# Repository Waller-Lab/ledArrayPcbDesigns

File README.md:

# ledArrayPcbDesigns
LED Array PCB Designs for various Arrays

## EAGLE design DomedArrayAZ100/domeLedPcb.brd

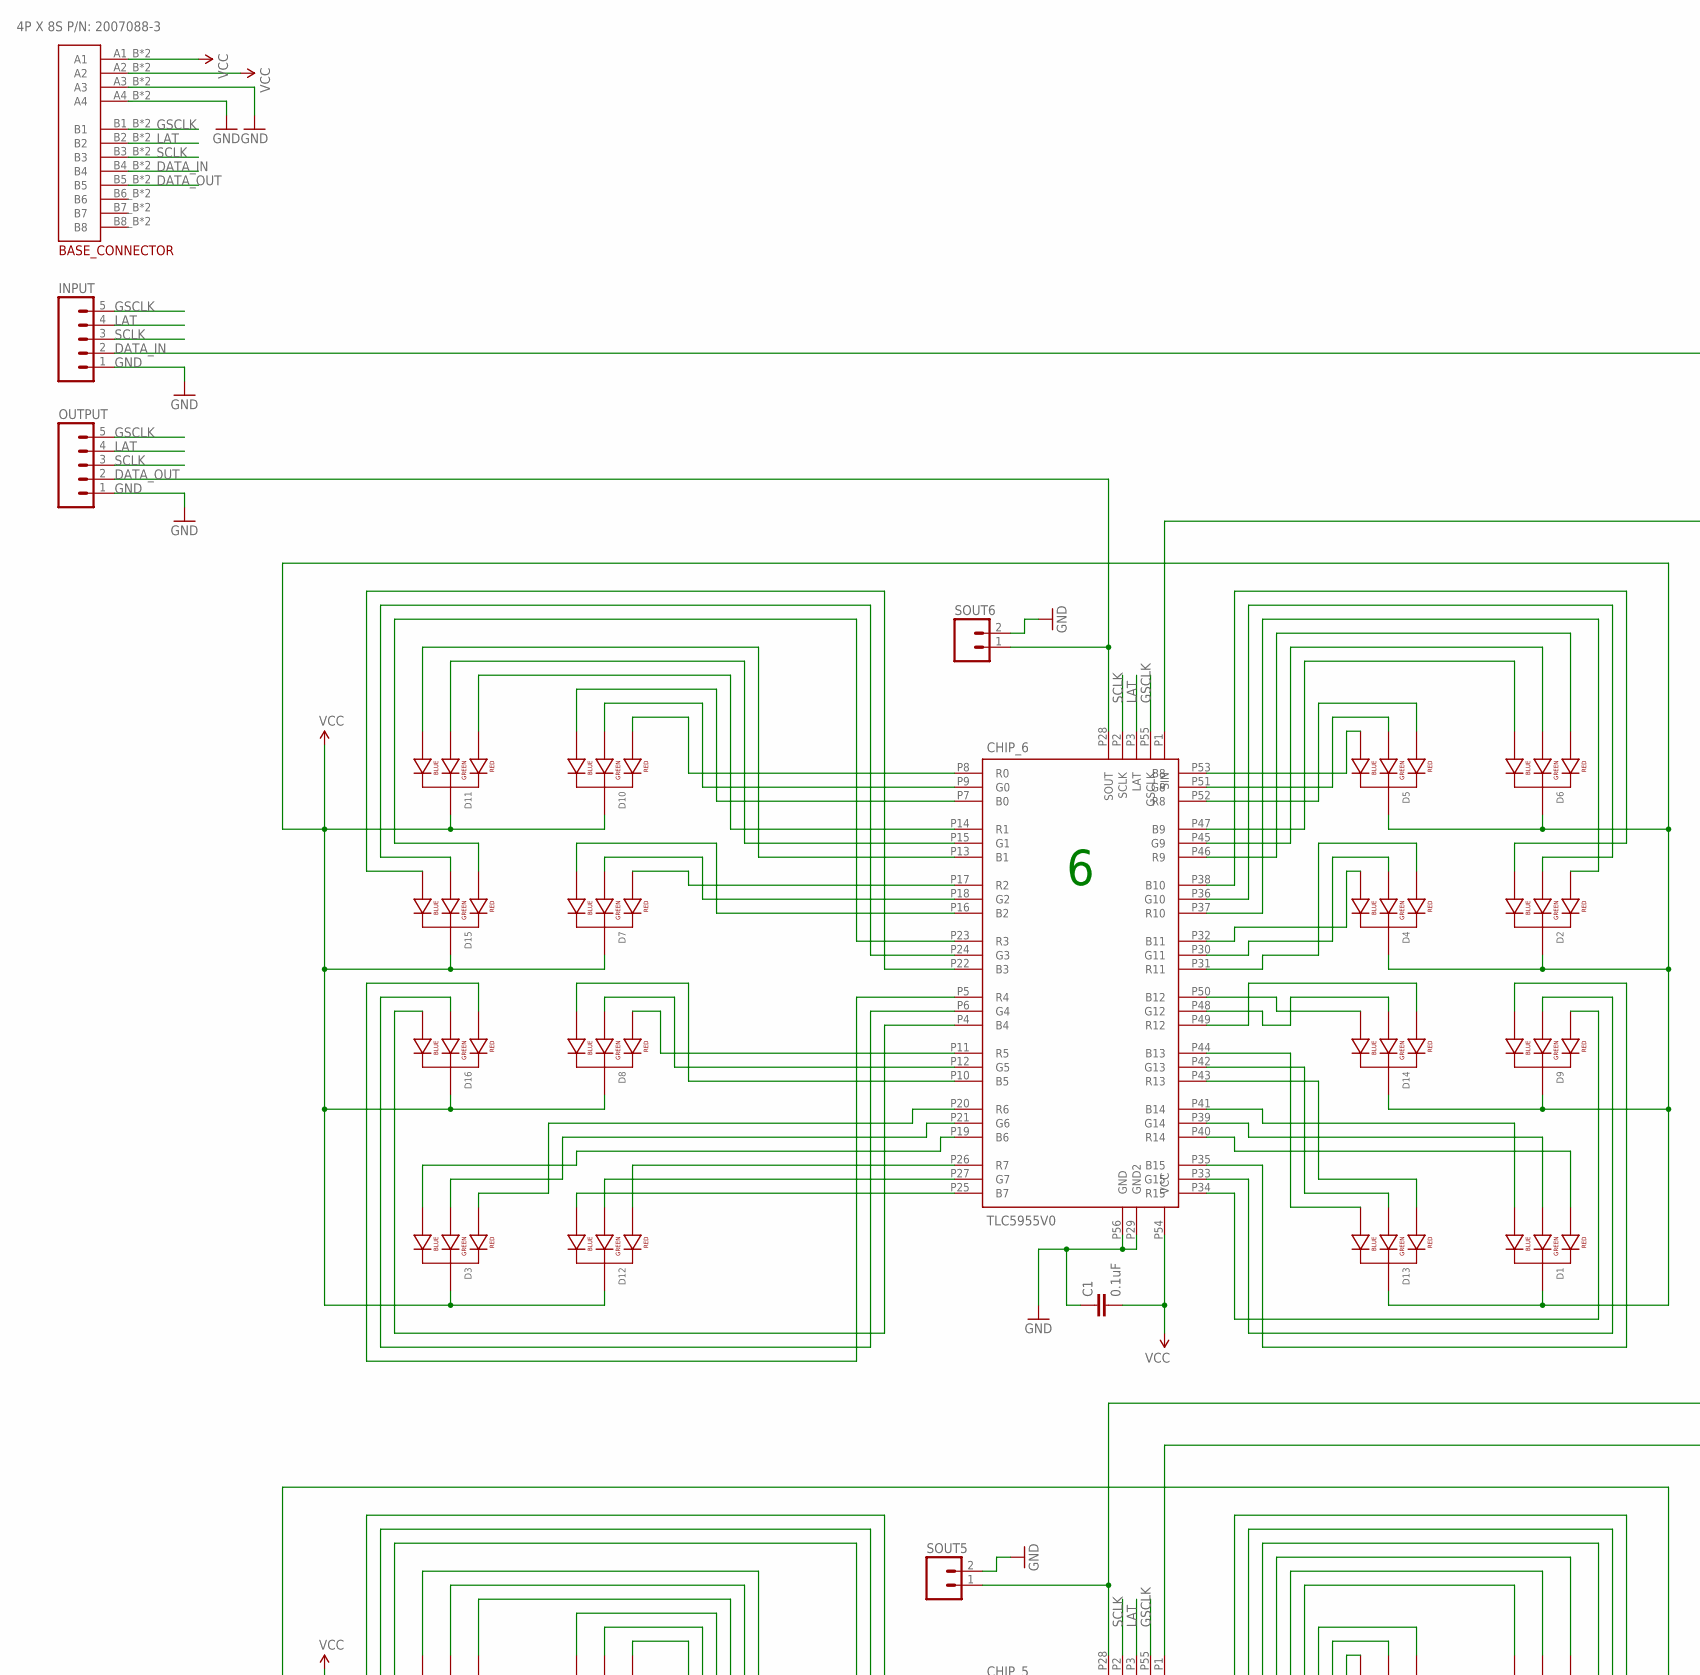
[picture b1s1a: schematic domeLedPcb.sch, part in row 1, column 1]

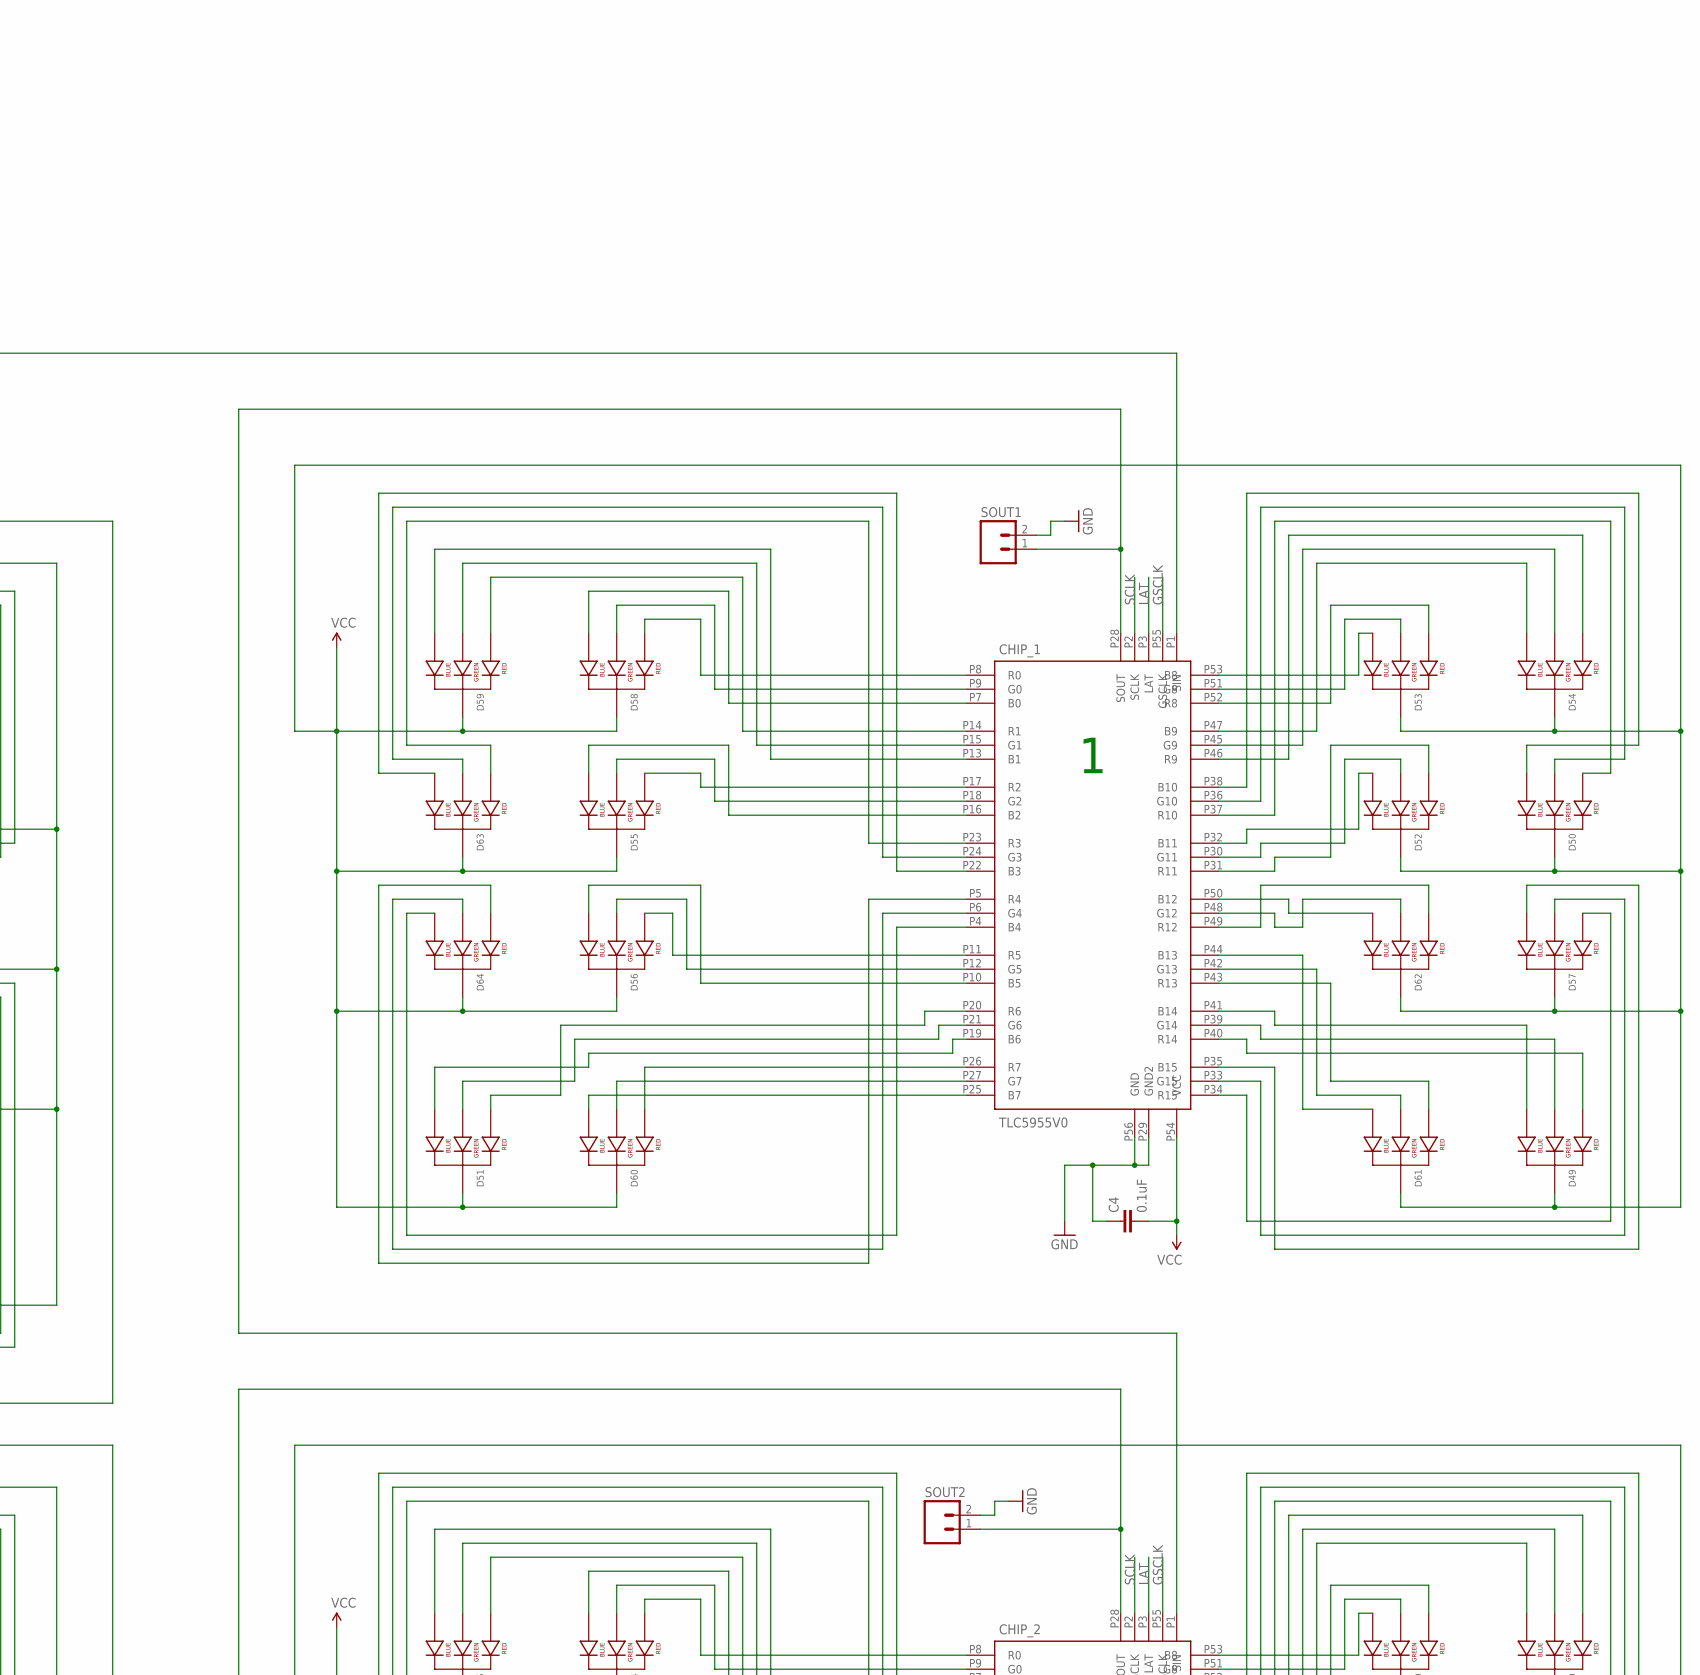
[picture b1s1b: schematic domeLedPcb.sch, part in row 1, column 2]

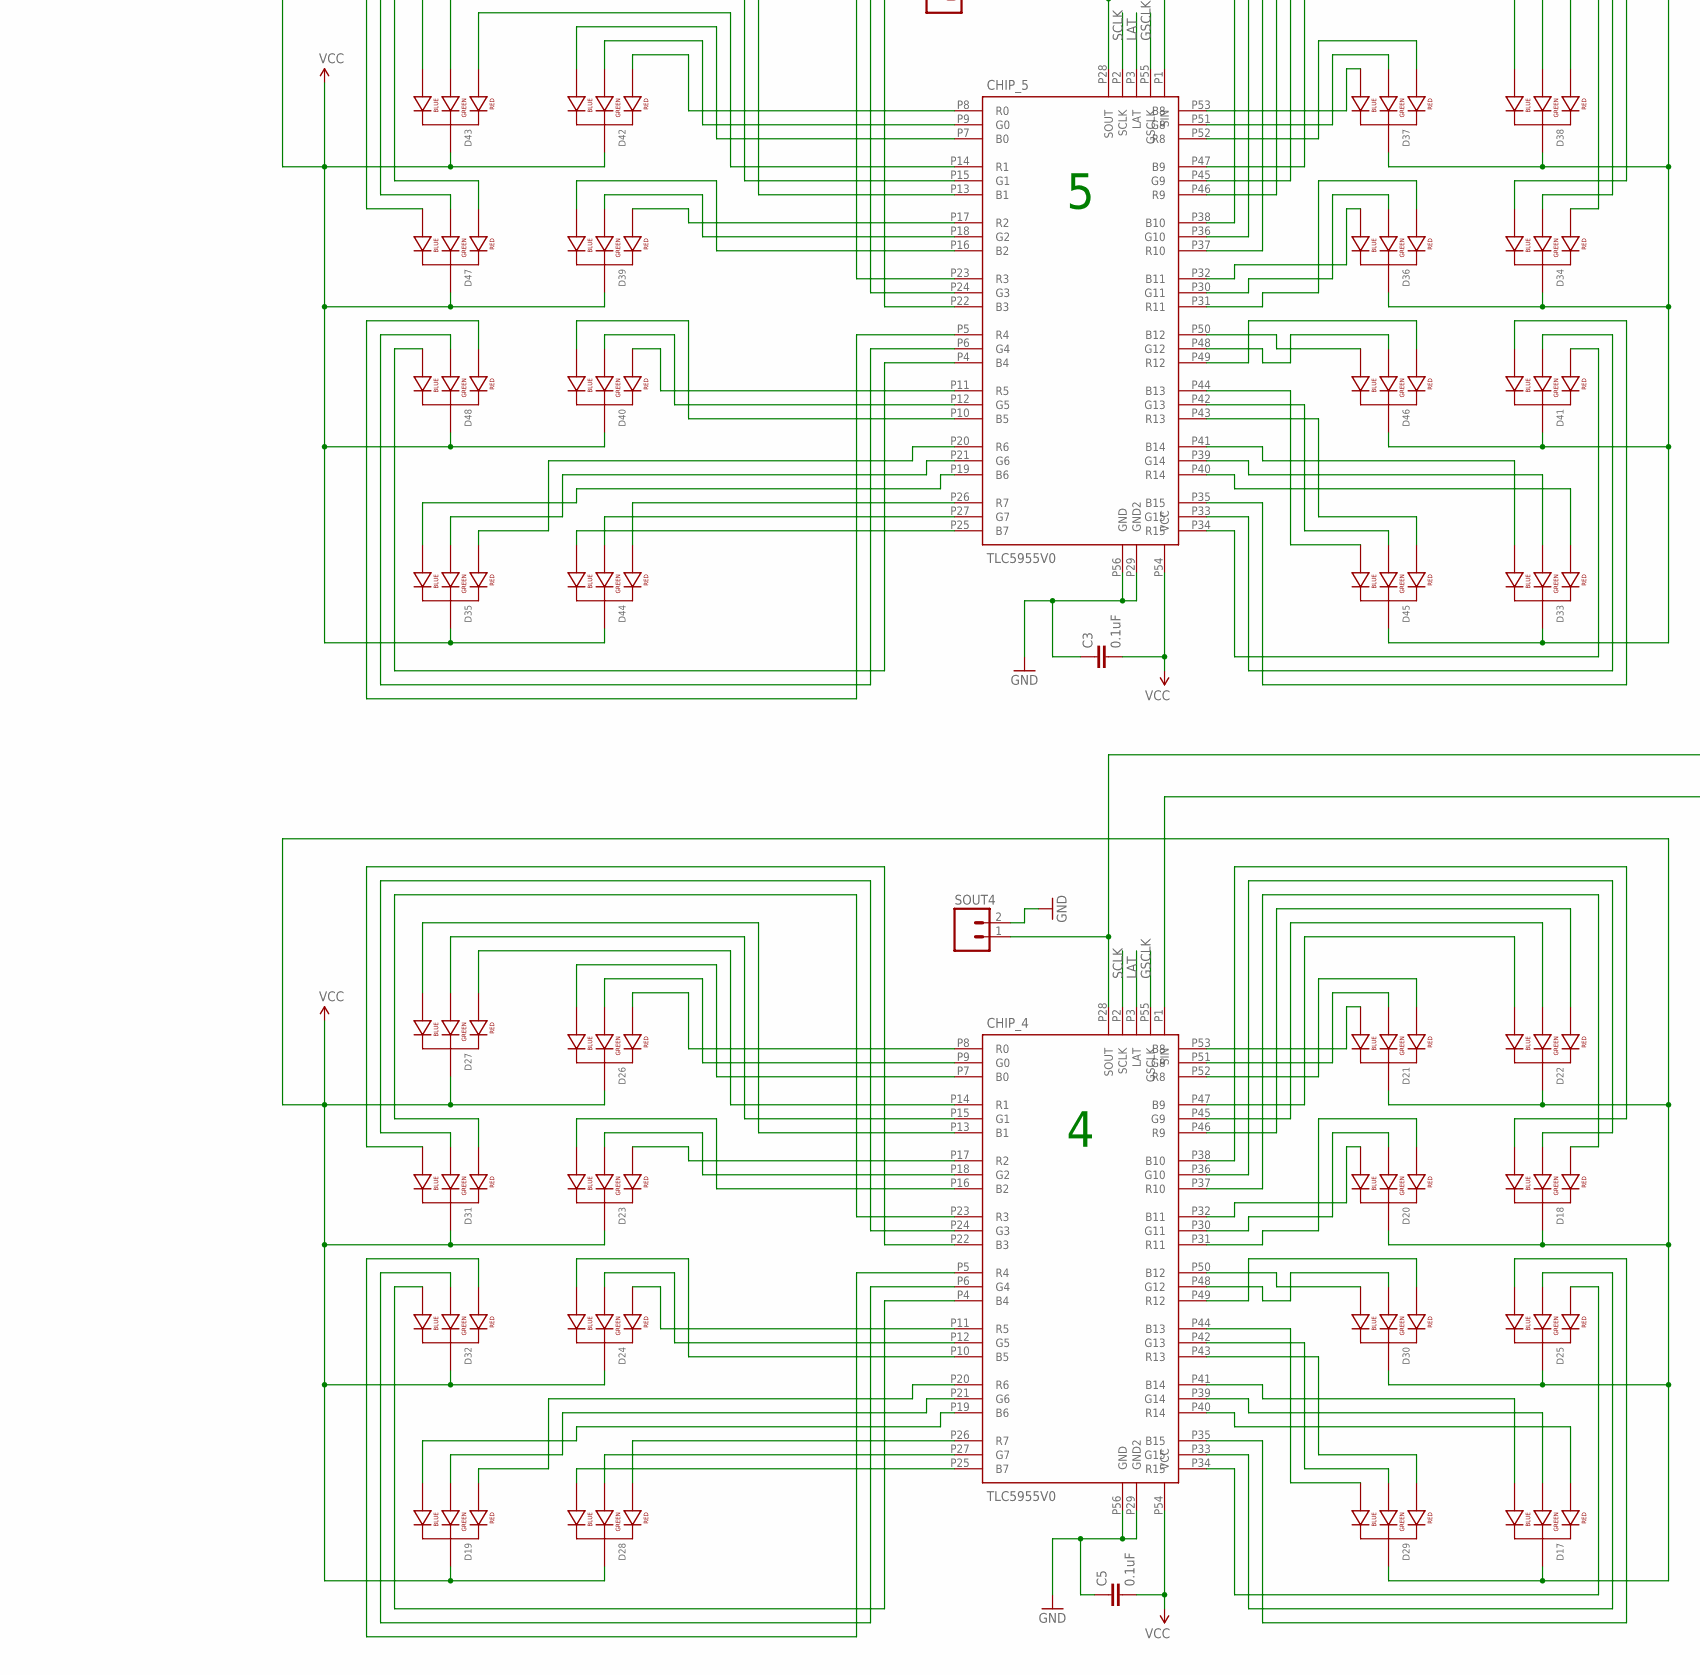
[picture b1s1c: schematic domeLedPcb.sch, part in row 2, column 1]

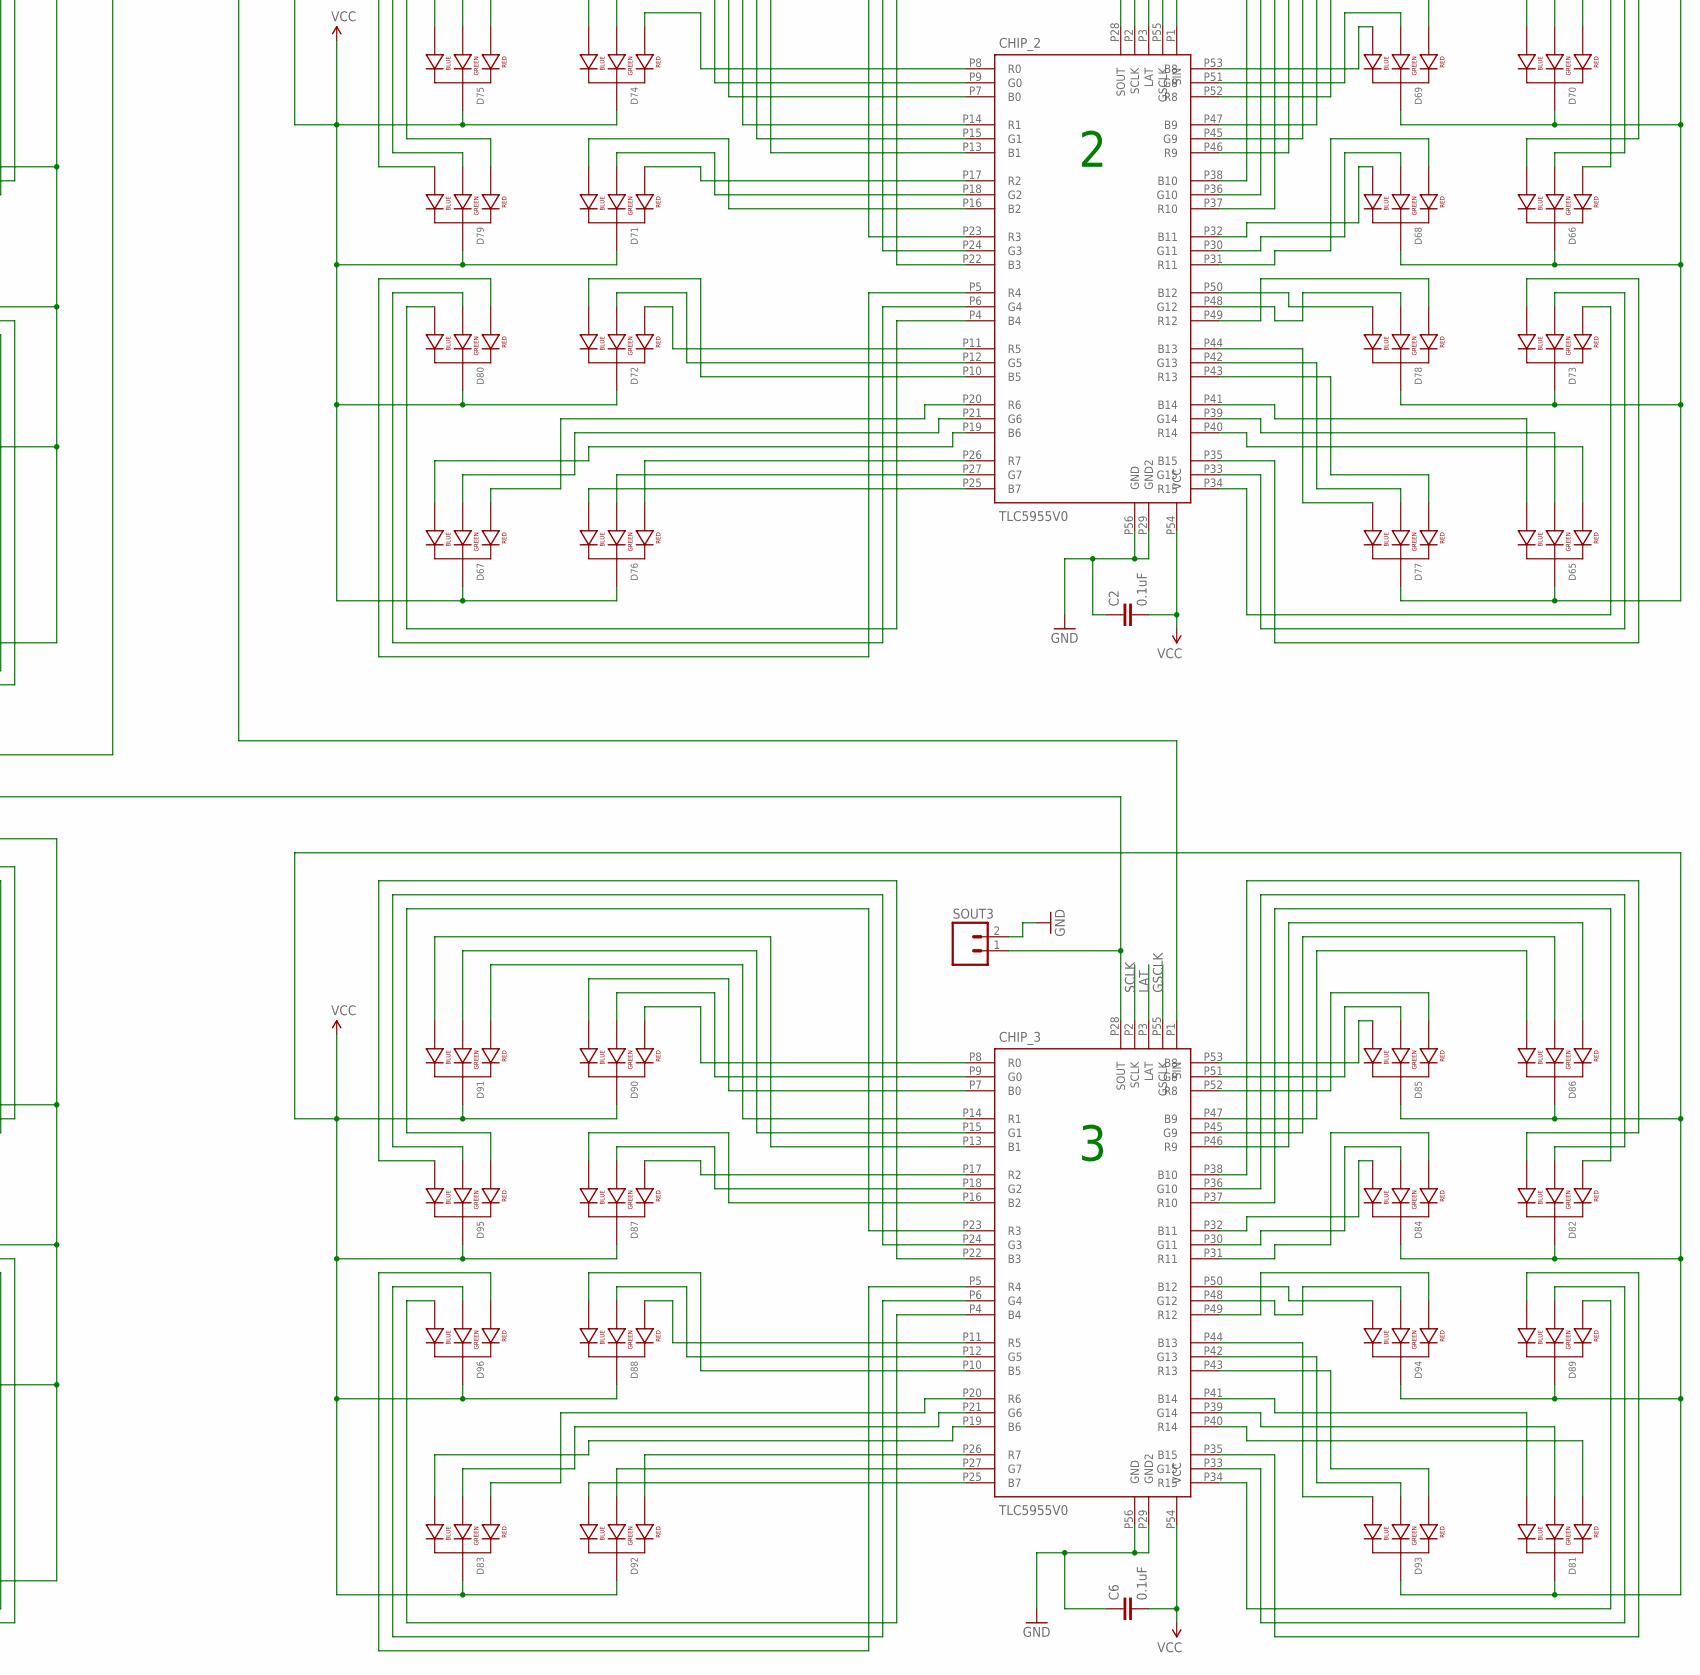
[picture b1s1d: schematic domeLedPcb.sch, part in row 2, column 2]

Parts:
BASE_CONNECTOR: 4POWER_8SIGNALMATING_BOARD; 4POWER_8SIGNAL
C1, C2, C3, C4, C5, C6: 0.1uF; 0603-CAP
CHIP_1, CHIP_2, CHIP_3, CHIP_4, CHIP_5, CHIP_6: TLC5955V0; 56-HTSSOP
D1, D2, D3, D4, D5, D6, D7, D8, D9, D10, D12, D13, D14, D15, D16, D17, D18, D19, D20, D21, D22, D23, D24, D25, D26, D27, D28, D29, D30, D31, D32, D33, D34, D36, D37, D38, D39, D40, D41, D42, D43, D44, D45, D46, D47, D48, D49, D50, D51, D52, D53, D54, D55, D56, D57, D58, D59, D60, D61, D62, D63, D64, D65, D66, D67, D68, D69, D70, D71, D72, D73, D74, D75, D76, D77, D78, D79, D80, D81, D82, D83, D84, D85, D86, D87, D88, D89, D90, D91, D92, D93, D94, D95, D96: LED-RGB-CC-THRUCLEAR; LED-RGB-THRU
D11: LED-RGB-CC-THRUDIFFUSE; LED-RGB-THRU
D35: 1; LED-RGB-THRU
INPUT: 1X05_LOCK_LONGPADS
OUTPUT: 1X05_LOCK_LONGPADS
SOUT1, SOUT2, SOUT3, SOUT4, SOUT5, SOUT6: 1X02_LOCK

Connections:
DATA_IN: BASE_CONNECTOR.B4_B (B4), BASE_CONNECTOR.B4_T (B4), CHIP_1.P1 (SIN), INPUT.2
DATA_OUT: BASE_CONNECTOR.B5_B (B5), BASE_CONNECTOR.B5_T (B5), CHIP_6.P28 (SOUT), OUTPUT.2, SOUT6.1
GND: BASE_CONNECTOR.A3_B (A3), BASE_CONNECTOR.A3_T (A3), BASE_CONNECTOR.A4_B (A4), BASE_CONNECTOR.A4_T (A4), C1.1, C2.1, C3.1, C4.1, C5.1, C6.1, CHIP_1.P29 (GND2), CHIP_1.P56 (GND), CHIP_2.P29 (GND2), CHIP_2.P56 (GND), CHIP_3.P29 (GND2), CHIP_3.P56 (GND), CHIP_4.P29 (GND2), CHIP_4.P56 (GND), CHIP_5.P29 (GND2), CHIP_5.P56 (GND), CHIP_6.P29 (GND2), CHIP_6.P56 (GND), INPUT.1, OUTPUT.1, SOUT1.2, SOUT2.2, SOUT3.2, SOUT4.2, SOUT5.2, SOUT6.2
GSCLK: BASE_CONNECTOR.B1_B (B1), BASE_CONNECTOR.B1_T (B1), CHIP_1.P55 (GSCLK), CHIP_2.P55 (GSCLK), CHIP_3.P55 (GSCLK), CHIP_4.P55 (GSCLK), CHIP_5.P55 (GSCLK), CHIP_6.P55 (GSCLK), INPUT.5, OUTPUT.5
LAT: BASE_CONNECTOR.B2_B (B2), BASE_CONNECTOR.B2_T (B2), CHIP_1.P3 (LAT), CHIP_2.P3 (LAT), CHIP_3.P3 (LAT), CHIP_4.P3 (LAT), CHIP_5.P3 (LAT), CHIP_6.P3 (LAT), INPUT.4, OUTPUT.4
unnamed: CHIP_6.P8 (R0), D10.3 (RED_CATHODE)
unnamed: CHIP_6.P20 (R6), D3.3 (RED_CATHODE)
unnamed: CHIP_6.P7 (B0), D10.4 (BLUE_CATHODE)
unnamed: CHIP_6.P17 (R2), D7.3 (RED_CATHODE)
unnamed: CHIP_6.P18 (G2), D7.1 (GREEN_CATHODE)
unnamed: CHIP_6.P16 (B2), D7.4 (BLUE_CATHODE)
unnamed: CHIP_6.P14 (R1), D11.3 (RED_CATHODE)
unnamed: CHIP_6.P34 (R15), D9.3 (RED_CATHODE)
unnamed: CHIP_6.P15 (G1), D11.1 (GREEN_CATHODE)
unnamed: CHIP_6.P13 (B1), D11.4 (BLUE_CATHODE)
unnamed: CHIP_6.P26 (R7), D12.3 (RED_CATHODE)
unnamed: CHIP_6.P27 (G7), D12.1 (GREEN_CATHODE)
unnamed: CHIP_6.P25 (B7), D12.4 (BLUE_CATHODE)
unnamed: CHIP_6.P11 (R5), D8.3 (RED_CATHODE)
unnamed: CHIP_6.P12 (G5), D8.1 (GREEN_CATHODE)
unnamed: CHIP_6.P10 (B5), D8.4 (BLUE_CATHODE)
unnamed: CHIP_6.P21 (G6), D3.1 (GREEN_CATHODE)
unnamed: CHIP_6.P19 (B6), D3.4 (BLUE_CATHODE)
unnamed: CHIP_6.P4 (B4), D16.4 (BLUE_CATHODE)
unnamed: CHIP_6.P6 (G4), D16.1 (GREEN_CATHODE)
unnamed: CHIP_6.P5 (R4), D16.3 (RED_CATHODE)
unnamed: CHIP_6.P23 (R3), D15.3 (RED_CATHODE)
unnamed: CHIP_6.P24 (G3), D15.1 (GREEN_CATHODE)
unnamed: CHIP_6.P22 (B3), D15.4 (BLUE_CATHODE)
unnamed: CHIP_6.P33 (G15), D9.1 (GREEN_CATHODE)
unnamed: CHIP_6.P30 (G11), D4.1 (GREEN_CATHODE)
unnamed: CHIP_6.P31 (R11), D4.3 (RED_CATHODE)
unnamed: CHIP_6.P51 (G8), D5.1 (GREEN_CATHODE)
unnamed: CHIP_6.P53 (B8), D5.4 (BLUE_CATHODE)
unnamed: CHIP_6.P35 (B15), D9.4 (BLUE_CATHODE)
unnamed: CHIP_6.P52 (R8), D5.3 (RED_CATHODE)
unnamed: CHIP_6.P47 (B9), D6.4 (BLUE_CATHODE)
unnamed: CHIP_6.P45 (G9), D6.1 (GREEN_CATHODE)
unnamed: CHIP_6.P40 (R14), D1.3 (RED_CATHODE)
unnamed: CHIP_6.P37 (R10), D2.3 (RED_CATHODE)
unnamed: CHIP_6.P48 (G12), D14.1 (GREEN_CATHODE)
unnamed: CHIP_6.P41 (B14), D1.4 (BLUE_CATHODE)
unnamed: CHIP_6.P46 (R9), D6.3 (RED_CATHODE)
unnamed: CHIP_6.P43 (R13), D13.3 (RED_CATHODE)
unnamed: CHIP_6.P42 (G13), D13.1 (GREEN_CATHODE)
unnamed: CHIP_6.P44 (B13), D13.4 (BLUE_CATHODE)
unnamed: CHIP_6.P36 (G10), D2.1 (GREEN_CATHODE)
unnamed: CHIP_6.P38 (B10), D2.4 (BLUE_CATHODE)
unnamed: CHIP_6.P32 (B11), D4.4 (BLUE_CATHODE)
unnamed: CHIP_4.P8 (R0), D26.3 (RED_CATHODE)
unnamed: CHIP_6.P50 (B12), D14.4 (BLUE_CATHODE)
unnamed: CHIP_6.P49 (R12), D14.3 (RED_CATHODE)
unnamed: CHIP_4.P7 (B0), D26.4 (BLUE_CATHODE)
unnamed: CHIP_6.P39 (G14), D1.1 (GREEN_CATHODE)
unnamed: CHIP_4.P17 (R2), D23.3 (RED_CATHODE)
unnamed: CHIP_4.P18 (G2), D23.1 (GREEN_CATHODE)
unnamed: CHIP_4.P16 (B2), D23.4 (BLUE_CATHODE)
unnamed: CHIP_4.P14 (R1), D27.3 (RED_CATHODE)
unnamed: CHIP_4.P15 (G1), D27.1 (GREEN_CATHODE)
unnamed: CHIP_4.P13 (B1), D27.4 (BLUE_CATHODE)
unnamed: CHIP_4.P26 (R7), D28.3 (RED_CATHODE)
unnamed: CHIP_4.P27 (G7), D28.1 (GREEN_CATHODE)
unnamed: CHIP_4.P25 (B7), D28.4 (BLUE_CATHODE)
unnamed: CHIP_4.P11 (R5), D24.3 (RED_CATHODE)
unnamed: CHIP_4.P12 (G5), D24.1 (GREEN_CATHODE)
unnamed: CHIP_4.P10 (B5), D24.4 (BLUE_CATHODE)
unnamed: CHIP_4.P20 (R6), D19.3 (RED_CATHODE)
unnamed: CHIP_4.P21 (G6), D19.1 (GREEN_CATHODE)
unnamed: CHIP_4.P19 (B6), D19.4 (BLUE_CATHODE)
unnamed: CHIP_4.P4 (B4), D32.4 (BLUE_CATHODE)
unnamed: CHIP_4.P6 (G4), D32.1 (GREEN_CATHODE)
unnamed: CHIP_4.P5 (R4), D32.3 (RED_CATHODE)
unnamed: CHIP_4.P23 (R3), D31.3 (RED_CATHODE)
unnamed: CHIP_4.P24 (G3), D31.1 (GREEN_CATHODE)
unnamed: CHIP_4.P22 (B3), D31.4 (BLUE_CATHODE)
unnamed: CHIP_4.P53 (B8), D21.4 (BLUE_CATHODE)
unnamed: CHIP_4.P52 (R8), D21.3 (RED_CATHODE)
unnamed: CHIP_4.P47 (B9), D22.4 (BLUE_CATHODE)
unnamed: CHIP_4.P45 (G9), D22.1 (GREEN_CATHODE)
unnamed: CHIP_4.P37 (R10), D18.3 (RED_CATHODE)
unnamed: CHIP_4.P30 (G11), D20.1 (GREEN_CATHODE)
unnamed: CHIP_4.P31 (R11), D20.3 (RED_CATHODE)
unnamed: CHIP_4.P51 (G8), D21.1 (GREEN_CATHODE)
unnamed: CHIP_4.P46 (R9), D22.3 (RED_CATHODE)
unnamed: CHIP_4.P36 (G10), D18.1 (GREEN_CATHODE)
unnamed: CHIP_4.P38 (B10), D18.4 (BLUE_CATHODE)
unnamed: CHIP_4.P32 (B11), D20.4 (BLUE_CATHODE)
unnamed: CHIP_4.P34 (R15), D25.3 (RED_CATHODE)
unnamed: CHIP_4.P33 (G15), D25.1 (GREEN_CATHODE)
unnamed: CHIP_4.P35 (B15), D25.4 (BLUE_CATHODE)
unnamed: CHIP_4.P40 (R14), D17.3 (RED_CATHODE)
unnamed: CHIP_4.P41 (B14), D17.4 (BLUE_CATHODE)
unnamed: CHIP_4.P43 (R13), D29.3 (RED_CATHODE)
unnamed: CHIP_4.P42 (G13), D29.1 (GREEN_CATHODE)
unnamed: CHIP_4.P44 (B13), D29.4 (BLUE_CATHODE)
unnamed: CHIP_4.P50 (B12), D30.4 (BLUE_CATHODE)
unnamed: CHIP_4.P49 (R12), D30.3 (RED_CATHODE)
unnamed: CHIP_4.P39 (G14), D17.1 (GREEN_CATHODE)
unnamed: CHIP_4.P48 (G12), D30.1 (GREEN_CATHODE)
unnamed: CHIP_5.P8 (R0), D42.3 (RED_CATHODE)
unnamed: CHIP_5.P7 (B0), D42.4 (BLUE_CATHODE)
unnamed: CHIP_5.P17 (R2), D39.3 (RED_CATHODE)
unnamed: CHIP_5.P18 (G2), D39.1 (GREEN_CATHODE)
unnamed: CHIP_5.P16 (B2), D39.4 (BLUE_CATHODE)
unnamed: CHIP_5.P14 (R1), D43.3 (RED_CATHODE)
unnamed: CHIP_5.P15 (G1), D43.1 (GREEN_CATHODE)
unnamed: CHIP_5.P13 (B1), D43.4 (BLUE_CATHODE)
unnamed: CHIP_5.P26 (R7), D44.3 (RED_CATHODE)
unnamed: CHIP_5.P27 (G7), D44.1 (GREEN_CATHODE)
unnamed: CHIP_5.P25 (B7), D44.4 (BLUE_CATHODE)
unnamed: CHIP_5.P11 (R5), D40.3 (RED_CATHODE)
unnamed: CHIP_5.P12 (G5), D40.1 (GREEN_CATHODE)
unnamed: CHIP_5.P10 (B5), D40.4 (BLUE_CATHODE)
unnamed: CHIP_5.P20 (R6), D35.3 (RED_CATHODE)
unnamed: CHIP_5.P21 (G6), D35.1 (GREEN_CATHODE)
unnamed: CHIP_5.P19 (B6), D35.4 (BLUE_CATHODE)
unnamed: CHIP_5.P4 (B4), D48.4 (BLUE_CATHODE)
unnamed: CHIP_5.P6 (G4), D48.1 (GREEN_CATHODE)
unnamed: CHIP_5.P5 (R4), D48.3 (RED_CATHODE)
unnamed: CHIP_5.P23 (R3), D47.3 (RED_CATHODE)
unnamed: CHIP_5.P24 (G3), D47.1 (GREEN_CATHODE)
unnamed: CHIP_5.P22 (B3), D47.4 (BLUE_CATHODE)
unnamed: CHIP_5.P53 (B8), D37.4 (BLUE_CATHODE)
unnamed: CHIP_5.P52 (R8), D37.3 (RED_CATHODE)
unnamed: CHIP_5.P47 (B9), D38.4 (BLUE_CATHODE)
unnamed: CHIP_5.P45 (G9), D38.1 (GREEN_CATHODE)
unnamed: CHIP_5.P37 (R10), D34.3 (RED_CATHODE)
unnamed: CHIP_5.P30 (G11), D36.1 (GREEN_CATHODE)
unnamed: CHIP_5.P31 (R11), D36.3 (RED_CATHODE)
unnamed: CHIP_5.P51 (G8), D37.1 (GREEN_CATHODE)
unnamed: CHIP_5.P46 (R9), D38.3 (RED_CATHODE)
unnamed: CHIP_5.P36 (G10), D34.1 (GREEN_CATHODE)
unnamed: CHIP_5.P38 (B10), D34.4 (BLUE_CATHODE)
unnamed: CHIP_5.P32 (B11), D36.4 (BLUE_CATHODE)
unnamed: CHIP_5.P34 (R15), D41.3 (RED_CATHODE)
unnamed: CHIP_5.P33 (G15), D41.1 (GREEN_CATHODE)
unnamed: CHIP_5.P35 (B15), D41.4 (BLUE_CATHODE)
unnamed: CHIP_5.P40 (R14), D33.3 (RED_CATHODE)
unnamed: CHIP_5.P41 (B14), D33.4 (BLUE_CATHODE)
unnamed: CHIP_5.P43 (R13), D45.3 (RED_CATHODE)
unnamed: CHIP_5.P42 (G13), D45.1 (GREEN_CATHODE)
unnamed: CHIP_5.P44 (B13), D45.4 (BLUE_CATHODE)
unnamed: CHIP_5.P50 (B12), D46.4 (BLUE_CATHODE)
unnamed: CHIP_5.P49 (R12), D46.3 (RED_CATHODE)
unnamed: CHIP_5.P39 (G14), D33.1 (GREEN_CATHODE)
unnamed: CHIP_5.P48 (G12), D46.1 (GREEN_CATHODE)
unnamed: CHIP_1.P8 (R0), D58.3 (RED_CATHODE)
unnamed: CHIP_1.P7 (B0), D58.4 (BLUE_CATHODE)
unnamed: CHIP_1.P17 (R2), D55.3 (RED_CATHODE)
unnamed: CHIP_1.P18 (G2), D55.1 (GREEN_CATHODE)
unnamed: CHIP_1.P16 (B2), D55.4 (BLUE_CATHODE)
unnamed: CHIP_1.P14 (R1), D59.3 (RED_CATHODE)
unnamed: CHIP_1.P15 (G1), D59.1 (GREEN_CATHODE)
unnamed: CHIP_1.P13 (B1), D59.4 (BLUE_CATHODE)
unnamed: CHIP_1.P26 (R7), D60.3 (RED_CATHODE)
unnamed: CHIP_1.P27 (G7), D60.1 (GREEN_CATHODE)
unnamed: CHIP_1.P25 (B7), D60.4 (BLUE_CATHODE)
unnamed: CHIP_1.P11 (R5), D56.3 (RED_CATHODE)
unnamed: CHIP_1.P12 (G5), D56.1 (GREEN_CATHODE)
unnamed: CHIP_1.P10 (B5), D56.4 (BLUE_CATHODE)
unnamed: CHIP_1.P20 (R6), D51.3 (RED_CATHODE)
unnamed: CHIP_1.P21 (G6), D51.1 (GREEN_CATHODE)
unnamed: CHIP_1.P19 (B6), D51.4 (BLUE_CATHODE)
unnamed: CHIP_1.P4 (B4), D64.4 (BLUE_CATHODE)
unnamed: CHIP_1.P6 (G4), D64.1 (GREEN_CATHODE)
unnamed: CHIP_1.P5 (R4), D64.3 (RED_CATHODE)
unnamed: CHIP_1.P23 (R3), D63.3 (RED_CATHODE)
unnamed: CHIP_1.P24 (G3), D63.1 (GREEN_CATHODE)
unnamed: CHIP_1.P22 (B3), D63.4 (BLUE_CATHODE)
unnamed: CHIP_1.P53 (B8), D53.4 (BLUE_CATHODE)
unnamed: CHIP_1.P52 (R8), D53.3 (RED_CATHODE)
unnamed: CHIP_1.P47 (B9), D54.4 (BLUE_CATHODE)
unnamed: CHIP_1.P45 (G9), D54.1 (GREEN_CATHODE)
unnamed: CHIP_1.P37 (R10), D50.3 (RED_CATHODE)
unnamed: CHIP_1.P30 (G11), D52.1 (GREEN_CATHODE)
unnamed: CHIP_1.P31 (R11), D52.3 (RED_CATHODE)
unnamed: CHIP_1.P51 (G8), D53.1 (GREEN_CATHODE)
unnamed: CHIP_1.P46 (R9), D54.3 (RED_CATHODE)
unnamed: CHIP_1.P36 (G10), D50.1 (GREEN_CATHODE)
unnamed: CHIP_1.P38 (B10), D50.4 (BLUE_CATHODE)
unnamed: CHIP_1.P32 (B11), D52.4 (BLUE_CATHODE)
unnamed: CHIP_1.P34 (R15), D57.3 (RED_CATHODE)
unnamed: CHIP_1.P33 (G15), D57.1 (GREEN_CATHODE)
unnamed: CHIP_1.P35 (B15), D57.4 (BLUE_CATHODE)
unnamed: CHIP_1.P40 (R14), D49.3 (RED_CATHODE)
unnamed: CHIP_1.P41 (B14), D49.4 (BLUE_CATHODE)
unnamed: CHIP_1.P43 (R13), D61.3 (RED_CATHODE)
unnamed: CHIP_1.P42 (G13), D61.1 (GREEN_CATHODE)
unnamed: CHIP_1.P44 (B13), D61.4 (BLUE_CATHODE)
unnamed: CHIP_1.P50 (B12), D62.4 (BLUE_CATHODE)
unnamed: CHIP_1.P49 (R12), D62.3 (RED_CATHODE)
unnamed: CHIP_1.P39 (G14), D49.1 (GREEN_CATHODE)
unnamed: CHIP_1.P48 (G12), D62.1 (GREEN_CATHODE)
unnamed: CHIP_2.P8 (R0), D74.3 (RED_CATHODE)
unnamed: CHIP_2.P7 (B0), D74.4 (BLUE_CATHODE)
unnamed: CHIP_2.P17 (R2), D71.3 (RED_CATHODE)
unnamed: CHIP_2.P18 (G2), D71.1 (GREEN_CATHODE)
unnamed: CHIP_2.P16 (B2), D71.4 (BLUE_CATHODE)
unnamed: CHIP_2.P14 (R1), D75.3 (RED_CATHODE)
unnamed: CHIP_2.P15 (G1), D75.1 (GREEN_CATHODE)
unnamed: CHIP_2.P13 (B1), D75.4 (BLUE_CATHODE)
unnamed: CHIP_2.P26 (R7), D76.3 (RED_CATHODE)
unnamed: CHIP_2.P27 (G7), D76.1 (GREEN_CATHODE)
unnamed: CHIP_2.P25 (B7), D76.4 (BLUE_CATHODE)
unnamed: CHIP_2.P11 (R5), D72.3 (RED_CATHODE)
unnamed: CHIP_2.P12 (G5), D72.1 (GREEN_CATHODE)
unnamed: CHIP_2.P10 (B5), D72.4 (BLUE_CATHODE)
unnamed: CHIP_2.P20 (R6), D67.3 (RED_CATHODE)
unnamed: CHIP_2.P21 (G6), D67.1 (GREEN_CATHODE)
unnamed: CHIP_2.P19 (B6), D67.4 (BLUE_CATHODE)
unnamed: CHIP_2.P4 (B4), D80.4 (BLUE_CATHODE)
unnamed: CHIP_2.P6 (G4), D80.1 (GREEN_CATHODE)
unnamed: CHIP_2.P5 (R4), D80.3 (RED_CATHODE)
unnamed: CHIP_2.P23 (R3), D79.3 (RED_CATHODE)
unnamed: CHIP_2.P24 (G3), D79.1 (GREEN_CATHODE)
unnamed: CHIP_2.P22 (B3), D79.4 (BLUE_CATHODE)
unnamed: CHIP_2.P53 (B8), D69.4 (BLUE_CATHODE)
unnamed: CHIP_2.P52 (R8), D69.3 (RED_CATHODE)
unnamed: CHIP_2.P47 (B9), D70.4 (BLUE_CATHODE)
unnamed: CHIP_2.P45 (G9), D70.1 (GREEN_CATHODE)
unnamed: CHIP_2.P37 (R10), D66.3 (RED_CATHODE)
unnamed: CHIP_2.P30 (G11), D68.1 (GREEN_CATHODE)
unnamed: CHIP_2.P31 (R11), D68.3 (RED_CATHODE)
unnamed: CHIP_2.P51 (G8), D69.1 (GREEN_CATHODE)
unnamed: CHIP_2.P46 (R9), D70.3 (RED_CATHODE)
unnamed: CHIP_2.P36 (G10), D66.1 (GREEN_CATHODE)
unnamed: CHIP_2.P38 (B10), D66.4 (BLUE_CATHODE)
unnamed: CHIP_2.P32 (B11), D68.4 (BLUE_CATHODE)
unnamed: CHIP_2.P34 (R15), D73.3 (RED_CATHODE)
unnamed: CHIP_2.P33 (G15), D73.1 (GREEN_CATHODE)
unnamed: CHIP_2.P35 (B15), D73.4 (BLUE_CATHODE)
unnamed: CHIP_2.P40 (R14), D65.3 (RED_CATHODE)
unnamed: CHIP_2.P41 (B14), D65.4 (BLUE_CATHODE)
unnamed: CHIP_2.P43 (R13), D77.3 (RED_CATHODE)
unnamed: CHIP_2.P42 (G13), D77.1 (GREEN_CATHODE)
unnamed: CHIP_2.P44 (B13), D77.4 (BLUE_CATHODE)
unnamed: CHIP_2.P50 (B12), D78.4 (BLUE_CATHODE)
unnamed: CHIP_2.P49 (R12), D78.3 (RED_CATHODE)
unnamed: CHIP_2.P39 (G14), D65.1 (GREEN_CATHODE)
unnamed: CHIP_2.P48 (G12), D78.1 (GREEN_CATHODE)
unnamed: CHIP_3.P8 (R0), D90.3 (RED_CATHODE)
unnamed: CHIP_3.P7 (B0), D90.4 (BLUE_CATHODE)
unnamed: CHIP_3.P17 (R2), D87.3 (RED_CATHODE)
unnamed: CHIP_3.P18 (G2), D87.1 (GREEN_CATHODE)
unnamed: CHIP_3.P16 (B2), D87.4 (BLUE_CATHODE)
unnamed: CHIP_3.P14 (R1), D91.3 (RED_CATHODE)
unnamed: CHIP_3.P15 (G1), D91.1 (GREEN_CATHODE)
unnamed: CHIP_3.P13 (B1), D91.4 (BLUE_CATHODE)
unnamed: CHIP_3.P26 (R7), D92.3 (RED_CATHODE)
unnamed: CHIP_3.P27 (G7), D92.1 (GREEN_CATHODE)
unnamed: CHIP_3.P25 (B7), D92.4 (BLUE_CATHODE)
unnamed: CHIP_3.P11 (R5), D88.3 (RED_CATHODE)
unnamed: CHIP_3.P12 (G5), D88.1 (GREEN_CATHODE)
unnamed: CHIP_3.P10 (B5), D88.4 (BLUE_CATHODE)
unnamed: CHIP_3.P20 (R6), D83.3 (RED_CATHODE)
unnamed: CHIP_3.P21 (G6), D83.1 (GREEN_CATHODE)
unnamed: CHIP_3.P19 (B6), D83.4 (BLUE_CATHODE)
unnamed: CHIP_3.P4 (B4), D96.4 (BLUE_CATHODE)
unnamed: CHIP_3.P6 (G4), D96.1 (GREEN_CATHODE)
unnamed: CHIP_3.P5 (R4), D96.3 (RED_CATHODE)
unnamed: CHIP_3.P23 (R3), D95.3 (RED_CATHODE)
unnamed: CHIP_3.P24 (G3), D95.1 (GREEN_CATHODE)
unnamed: CHIP_3.P22 (B3), D95.4 (BLUE_CATHODE)
unnamed: CHIP_3.P53 (B8), D85.4 (BLUE_CATHODE)
unnamed: CHIP_3.P52 (R8), D85.3 (RED_CATHODE)
unnamed: CHIP_3.P47 (B9), D86.4 (BLUE_CATHODE)
unnamed: CHIP_3.P45 (G9), D86.1 (GREEN_CATHODE)
unnamed: CHIP_3.P37 (R10), D82.3 (RED_CATHODE)
unnamed: CHIP_3.P30 (G11), D84.1 (GREEN_CATHODE)
unnamed: CHIP_3.P31 (R11), D84.3 (RED_CATHODE)
unnamed: CHIP_3.P51 (G8), D85.1 (GREEN_CATHODE)
unnamed: CHIP_3.P46 (R9), D86.3 (RED_CATHODE)
unnamed: CHIP_3.P36 (G10), D82.1 (GREEN_CATHODE)
unnamed: CHIP_3.P38 (B10), D82.4 (BLUE_CATHODE)
unnamed: CHIP_3.P32 (B11), D84.4 (BLUE_CATHODE)
unnamed: CHIP_3.P34 (R15), D89.3 (RED_CATHODE)
unnamed: CHIP_3.P33 (G15), D89.1 (GREEN_CATHODE)
unnamed: CHIP_3.P35 (B15), D89.4 (BLUE_CATHODE)
unnamed: CHIP_3.P40 (R14), D81.3 (RED_CATHODE)
unnamed: CHIP_3.P41 (B14), D81.4 (BLUE_CATHODE)
unnamed: CHIP_3.P43 (R13), D93.3 (RED_CATHODE)
unnamed: CHIP_3.P42 (G13), D93.1 (GREEN_CATHODE)
unnamed: CHIP_3.P44 (B13), D93.4 (BLUE_CATHODE)
unnamed: CHIP_3.P50 (B12), D94.4 (BLUE_CATHODE)
unnamed: CHIP_3.P49 (R12), D94.3 (RED_CATHODE)
unnamed: CHIP_3.P39 (G14), D81.1 (GREEN_CATHODE)
unnamed: CHIP_3.P48 (G12), D94.1 (GREEN_CATHODE)
unnamed: CHIP_3.P28 (SOUT), CHIP_4.P1 (SIN), SOUT3.1
unnamed: CHIP_5.P28 (SOUT), CHIP_6.P1 (SIN), SOUT5.1
unnamed: CHIP_4.P28 (SOUT), CHIP_5.P1 (SIN), SOUT4.1
unnamed: CHIP_1.P28 (SOUT), CHIP_2.P1 (SIN), SOUT1.1
unnamed: CHIP_3.P9 (G0), D90.1 (GREEN_CATHODE)
unnamed: CHIP_5.P9 (G0), D42.1 (GREEN_CATHODE)
unnamed: CHIP_4.P9 (G0), D26.1 (GREEN_CATHODE)
unnamed: CHIP_2.P28 (SOUT), CHIP_3.P1 (SIN), SOUT2.1
unnamed: CHIP_6.P9 (G0), D10.1 (GREEN_CATHODE)
unnamed: CHIP_2.P9 (G0), D74.1 (GREEN_CATHODE)
unnamed: CHIP_1.P9 (G0), D58.1 (GREEN_CATHODE)
SCLK: BASE_CONNECTOR.B3_B (B3), BASE_CONNECTOR.B3_T (B3), CHIP_1.P2 (SCLK), CHIP_2.P2 (SCLK), CHIP_3.P2 (SCLK), CHIP_4.P2 (SCLK), CHIP_5.P2 (SCLK), CHIP_6.P2 (SCLK), INPUT.3, OUTPUT.3
VCC: BASE_CONNECTOR.A1_B (A1), BASE_CONNECTOR.A1_T (A1), BASE_CONNECTOR.A2_B (A2), BASE_CONNECTOR.A2_T (A2), C1.2, C2.2, C3.2, C4.2, C5.2, C6.2, CHIP_1.P54 (VCC), CHIP_2.P54 (VCC), CHIP_3.P54 (VCC), CHIP_4.P54 (VCC), CHIP_5.P54 (VCC), CHIP_6.P54 (VCC), D1.2 (CATHODE), D2.2 (CATHODE), D3.2 (CATHODE), D4.2 (CATHODE), D5.2 (CATHODE), D6.2 (CATHODE), D7.2 (CATHODE), D8.2 (CATHODE), D9.2 (CATHODE), D10.2 (CATHODE), D11.2 (CATHODE), D12.2 (CATHODE), D13.2 (CATHODE), D14.2 (CATHODE), D15.2 (CATHODE), D16.2 (CATHODE), D17.2 (CATHODE), D18.2 (CATHODE), D19.2 (CATHODE), D20.2 (CATHODE), D21.2 (CATHODE), D22.2 (CATHODE), D23.2 (CATHODE), D24.2 (CATHODE), D25.2 (CATHODE), D26.2 (CATHODE), D27.2 (CATHODE), D28.2 (CATHODE), D29.2 (CATHODE), D30.2 (CATHODE), D31.2 (CATHODE), D32.2 (CATHODE), D33.2 (CATHODE), D34.2 (CATHODE), D35.2 (CATHODE), D36.2 (CATHODE), D37.2 (CATHODE), D38.2 (CATHODE), D39.2 (CATHODE), D40.2 (CATHODE), D41.2 (CATHODE), D42.2 (CATHODE), D43.2 (CATHODE), D44.2 (CATHODE), D45.2 (CATHODE), D46.2 (CATHODE), D47.2 (CATHODE), D48.2 (CATHODE), D49.2 (CATHODE), D50.2 (CATHODE), D51.2 (CATHODE), D52.2 (CATHODE), D53.2 (CATHODE), D54.2 (CATHODE), D55.2 (CATHODE), D56.2 (CATHODE), D57.2 (CATHODE), D58.2 (CATHODE), D59.2 (CATHODE), D60.2 (CATHODE), D61.2 (CATHODE), D62.2 (CATHODE), D63.2 (CATHODE), D64.2 (CATHODE), D65.2 (CATHODE), D66.2 (CATHODE), D67.2 (CATHODE), D68.2 (CATHODE), D69.2 (CATHODE), D70.2 (CATHODE), D71.2 (CATHODE), D72.2 (CATHODE), D73.2 (CATHODE), D74.2 (CATHODE), D75.2 (CATHODE), D76.2 (CATHODE), D77.2 (CATHODE), D78.2 (CATHODE), D79.2 (CATHODE), D80.2 (CATHODE), D81.2 (CATHODE), D82.2 (CATHODE), D83.2 (CATHODE), D84.2 (CATHODE), D85.2 (CATHODE), D86.2 (CATHODE), D87.2 (CATHODE), D88.2 (CATHODE), D89.2 (CATHODE), D90.2 (CATHODE), D91.2 (CATHODE), D92.2 (CATHODE), D93.2 (CATHODE), D94.2 (CATHODE), D95.2 (CATHODE), D96.2 (CATHODE)

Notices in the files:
parts and their libraries:
SparkFun-Capacitors: Licensing: Creative Commons ShareAlike 4.0 International - https://creativecommons.org/licenses/by-sa/4.0
